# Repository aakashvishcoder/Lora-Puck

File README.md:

# Lora Puck

This is my version of a Lora Puck, which is a compact, low-power wireless communication module that can send and receive data from several kilometers away! This puck has several unique features and parts (as listed below), and includes a temperature sensor as well! This is one of my first ever PCBs, so it most definitely has some flaws!

# Features:
- USBC Receptacle
- Programmable Microcontroller

# Images:

# Build of Materials (BOM)

| Item | Description | Qty | Product link | Price w/ Tax ($) | Running Total |
|------|-------------|-----|--------------|------------------|---------------|
| Capacitor | 100nF (0.1uF) | 13 | [link](https://jlcpcb.com/partdetail/1877-CL05B104KO5NNNC/C1525) | $0.21 | $0.21 |
| Capacitor | 1uF | 2 | [link](https://jlcpcb.com/partdetail/53938-CL05A105KA5NQNC/C52923) | $0.06 | $0.27 |
| Capacitor | 47nF | 1 | [link](https://jlcpcb.com/partdetail/YAGEO-CC0402KRX7R9BB473/C1532) | $0.02 | $0.29 |
| Capacitor | 47pF | 1 | [link](https://jlcpcb.com/partdetail/YAGEO-CC0402JRNPO9BN470/C1549) | $0.01 | $0.30 |
| Capacitor | 1nF | 1 | [link](https://jlcpcb.com/partdetail/YAGEO-CC0402KRX7R9BB102/C1522) | $0.01 | $0.31 |
| Capacitor | 39pF | 1 | [link](https://jlcpcb.com/partdetail/YAGEO-CC0402JRNPO9BN390/C1548) | $0.01 | $0.32 |
| Capacitor | 3.3pF | 4 | [link](https://jlcpcb.com/partdetail/YAGEO-CC0402JRNPO9BN3R3/C1546) | $0.04 | $0.36 |
| Capacitor | 10uF | 2 | [link](https://jlcpcb.com/partdetail/SamsungElectro-CL05A106MQ5NUNC/C15525) | $0.06 | $0.42 |
| Capacitor | 470nF | 1 | [link](https://jlcpcb.com/partdetail/YAGEO-CC0402KRX7R9BB471/C1779) | $0.02 | $0.44 |
| Inductor | 15uH | 1 | [link](https://jlcpcb.com/partdetail/Sunlord-SDCL1005C150KTDF/C285676) | $0.05 | $0.49 |
| Inductor | 47nH | 1 | [link](https://jlcpcb.com/partdetail/JohansonTech-L-0402_47nH/C284438) | $0.05 | $0.54 |
| Inductor | 9.1nH | 1 | [link](https://jlcpcb.com/partdetail/JohansonTech-L-0402_9_1nH/C284437) | $0.05 | $0.59 |
| Ferrite Bead | Ferrite 0402 | 1 | [link](https://jlcpcb.com/partdetail/Sunlord-SDCL1005C4N7STDF/C8589) | $0.01 | $0.60 |
| Balun | Johanson 0900FM15K0039 | 1 | [link](https://jlcpcb.com/partdetail/JohansonTech-0900FM15K0039/C284439) | $0.85 | $1.45 |
| Resistor | 10k | 1 | [link](https://jlcpcb.com/partdetail/UNIROYAL-0402WGF1002TCE/C25804) | $0.01 | $1.46 |
| Resistor | 4.7k | 2 | [link](https://jlcpcb.com/partdetail/UNIROYAL-0402WGF4701TCE/C25867) | $0.02 | $1.48 |
| Resistor | 27.4Ω | 2 | [link](https://jlcpcb.com/partdetail/UNIROYAL-0402WGF270JTCE/C23154) | $0.02 | $1.50 |
| Resistor | 1k | 2 | [link](https://jlcpcb.com/partdetail/UNIROYAL-0402WGF1001TCE/C11702) | $0.02 | $1.52 |
| Resistor | 100Ω | 1 | [link](https://jlcpcb.com/partdetail/UNIROYAL-0402WGF1000TCE/C25086) | $0.01 | $1.53 |
| Resistor | 5.1k | 2 | [link](https://jlcpcb.com/partdetail/UNIROYAL-0402WGF5101TCE/C25905) | $0.02 | $1.55 |
| Switch | Tactile Button | 2 | [link](https://jlcpcb.com/partdetail/XKBConnectivity-TS1187ABAB/C318884) | $0.84 | $2.39 |
| USB Receptacle | USB-C 16P | 1 | [link](https://jlcpcb.com/partdetail/Korean_HropartsElec-TYPEC31M12/C165948) | $0.85 | $3.24 |
| IC | LoRa SX1262 | 1 | [link](https://jlcpcb.com/partdetail/Semtech-SX1262IMLTRT/C967207) | $6.50 | $9.74 |
| IC | RP2040 MCU | 1 | [link](https://jlcpcb.com/partdetail/RaspberryPi-RP2040/C2040) | $4.58 | $14.32 |
| IC | Flash W25Q128JVS | 1 | [link](https://jlcpcb.com/partdetail/Winbond-W25Q128JVSIQ/C97521) | $2.67 | $16.99 |
| IC | RF Switch PE4259 | 1 | [link](https://jlcpcb.com/partdetail/PeregrineSemiconductor-PE4259/C285440) | $1.20 | $18.19 |
| IC | Regulator AP2112K-3.3 | 1 | [link](https://jlcpcb.com/partdetail/DiodesInc-AP2112K3_3TRG1/C15630) | $0.12 | $18.31 |
| Sensor | SHTC3 Humidity/Temp | 1 | [link](https://jlcpcb.com/partdetail/Sensirion-SHTC3/C2844388) | $2.80 | $21.11 |
| Crystal | 32MHz 3225 | 1 | [link](https://jlcpcb.com/partdetail/YXC-X322532MSB4SI/C9003) | $0.32 | $21.43 |
| Crystal | 12MHz 3225 | 1 | [link](https://jlcpcb.com/partdetail/YXC-X322512MSB4SI/C9002) | $0.32 | $21.75 |
| LoRa-Puck PCB | PCBA board assembly | 1 | [link](https://cart.jlcpcb.com/) | $43.94 | $65.69 |

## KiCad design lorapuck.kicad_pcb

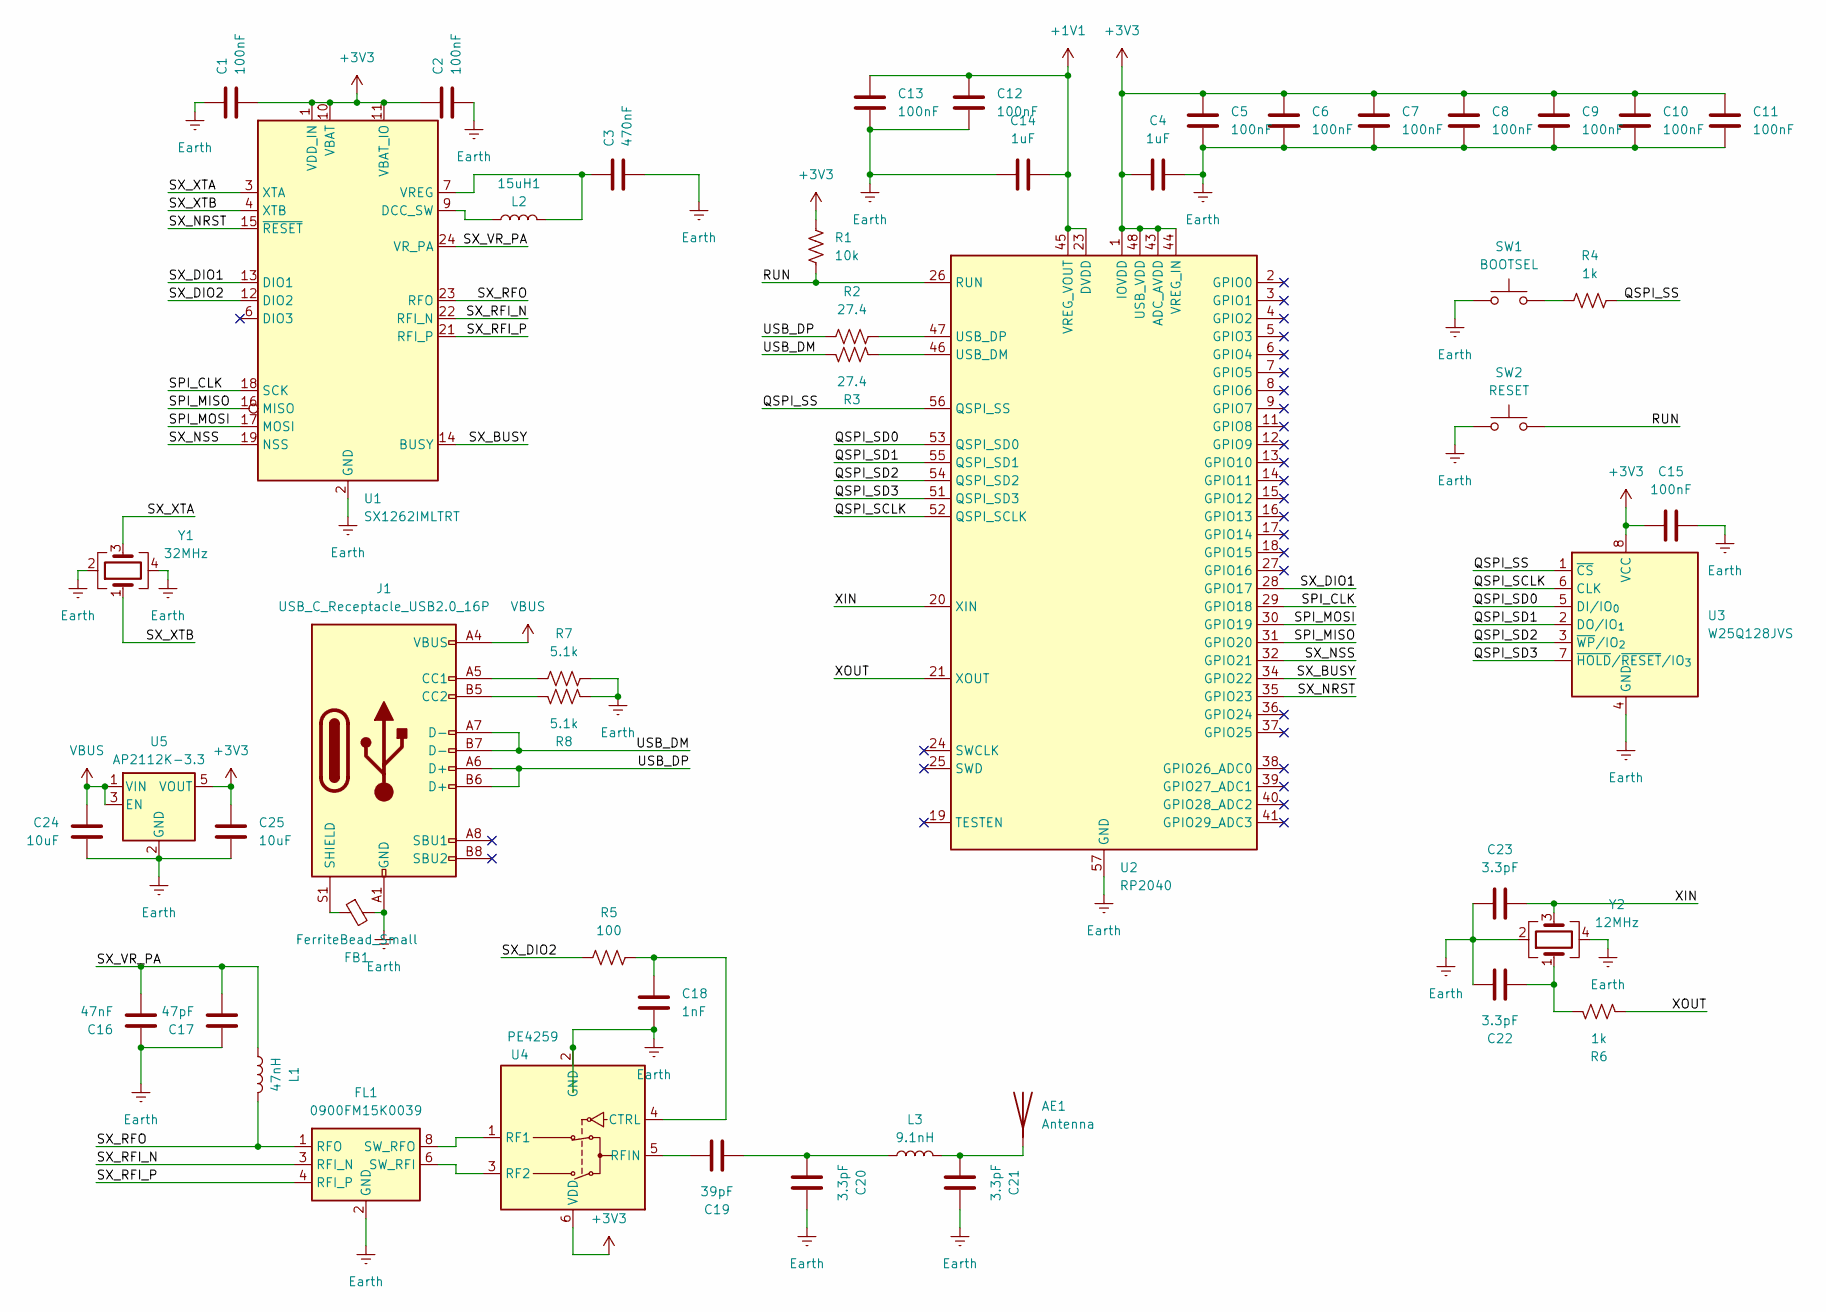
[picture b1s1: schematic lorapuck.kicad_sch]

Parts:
15uH1: L2; L_0402_1005Metric
AE1: Antenna; PinSocket_1x01_P2.54mm_Vertical
C1, C2, C5, C6, C7, C8, C9, C10, C11, C12, C13, C15: 100nF; C_0402_1005Metric
C3: 470nF; C_0402_1005Metric
C4, C14: 1uF; C_0402_1005Metric
C16: 47nF; C_0402_1005Metric
C17: 47pF; C_0402_1005Metric
C18: 1nF; C_0402_1005Metric
C19: 39pF; C_0402_1005Metric
C20, C21, C22, C23: 3.3pF; C_0402_1005Metric
C24, C25: 10uF; C_0402_1005Metric
FB1: FerriteBead_Small; L_0402_1005Metric
FL1: 0900FM15K0039; Balun_Johanson_0900FM15K0039
J1: USB_C_Receptacle_USB2.0_16P; USB_C_Receptacle_GCT_USB4105-xx-A_16P_TopMnt_Horizontal
L1: 47nH; L_0402_1005Metric
L3: 9.1nH; L_0402_1005Metric
R1: 10k; R_0402_1005Metric
R2, R3: 27.4; R_0402_1005Metric
R4, R6: 1k; R_0402_1005Metric
R5: 100; R_0402_1005Metric
R7, R8: 5.1k; R_0402_1005Metric
SW1: BOOTSEL; SW_Tactile_SPST_NO_Straight_CK_PTS636Sx25SMTRLFS
SW2: RESET; SW_Tactile_SPST_NO_Straight_CK_PTS636Sx25SMTRLFS
U1: SX1262IMLTRT; QFN-24-1EP_4x4mm_P0.5mm_EP2.6x2.6mm
U2: RP2040; QFN-56-1EP_7x7mm_P0.4mm_EP3.2x3.2mm
U3: W25Q128JVS; SOIC-8_5.3x5.3mm_P1.27mm
U4: PE4259; SOT-363_SC-70-6
U5: AP2112K-3.3; SOT-23-5
Y1: 32MHz; Crystal_SMD_3225-4Pin_3.2x2.5mm
Y2: 12MHz; Crystal_SMD_Abracon_ABM8G-4Pin_3.2x2.5mm

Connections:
+1V1: C12.2, C13.2, C14.2, U2.23 (DVDD), U2.45 (VREG_VOUT), U2.50 (DVDD)
+3V3: C1.2, C2.1, C4.1, C5.2, C6.2, C7.2, C8.2, C9.2, C10.2, C11.2, C15.2, C25.1, R1.1, U1.1 (VDD_IN), U1.10 (VBAT), U1.11 (VBAT_IO), U2.1 (IOVDD), U2.10 (IOVDD), U2.22 (IOVDD), U2.33 (IOVDD), U2.42 (IOVDD), U2.43 (ADC_AVDD), U2.44 (VREG_IN), U2.48 (USB_VDD), U2.49 (IOVDD), U3.8 (VCC), U4.6 (VDD), U5.5 (VOUT); also elsewhere on the board
/<NO NET>: U1.15 (~RESET), U2.35 (GPIO23)
/IO0: U2.2 (GPIO0); also elsewhere on the board
/IO1: U2.3 (GPIO1); also elsewhere on the board
/QSPI_SCLK: U2.52 (QSPI_SCLK), U3.6 (CLK)
/QSPI_SD0: U2.53 (QSPI_SD0), U3.5 (DI/IO_{0})
/QSPI_SD1: U2.55 (QSPI_SD1), U3.2 (DO/IO_{1})
/QSPI_SD2: U2.54 (QSPI_SD2), U3.3 (~WP/IO_{2})
/QSPI_SD3: U2.51 (QSPI_SD3), U3.7 (~HOLD/~RESET/IO_{3})
/QSPI_SS: R4.1, U2.56 (QSPI_SS), U3.1 (~CS)
/RUN: R1.2, SW2.2, U2.26 (RUN)
/SPI_CLK: U1.18 (SCK), U2.29 (GPIO18)
/SPI_MISO: U1.16 (MISO), U2.31 (GPIO20)
/SPI_MOSI: U1.17 (MOSI), U2.30 (GPIO19)
/SX_BUSY: U1.14 (BUSY), U2.34 (GPIO22)
/SX_DIO1: U1.13 (DIO1), U2.28 (GPIO17)
/SX_DIO2: R5.1, U1.12 (DIO2)
/SX_NSS: U1.19 (NSS), U2.32 (GPIO21)
/SX_RFI_N: FL1.3 (RFI_N), U1.22 (RFI_N)
/SX_RFI_P: FL1.4 (RFI_P), U1.21 (RFI_P)
/SX_RFO: FL1.1 (RFO), L1.2, U1.23 (RFO)
/SX_VR_PA: C16.2, C17.2, L1.1, U1.24 (VR_PA)
/SX_XTA: U1.3 (XTA), Y1.3
/SX_XTB: U1.4 (XTB), Y1.1
/USB_DM: J1.A7 (D-), J1.B7 (D-), R3.2
/USB_DP: J1.A6 (D+), J1.B6 (D+), R2.2
/XIN: C23.1, U2.20 (XIN), Y2.3
/XOUT: R6.2, U2.21 (XOUT)
Earth: C1.1, C2.2, C3.2, C4.2, C5.1, C6.1, C7.1, C8.1, C9.1, C10.1, C11.1, C12.1, C13.1, C14.1, C15.1, C16.1, C17.1, C18.2, C20.1, C21.1, C22.1, C23.2, C24.2, C25.2, FB1.2, FL1.2 (GND), FL1.5 (GND), FL1.7 (GND), FL1.9 (GND), FL1.10 (GND), J1.A1 (GND), J1.A12 (GND), J1.B1 (GND), J1.B12 (GND), R7.2, R8.2, SW1.1, SW2.1, U1.2 (GND), U1.5 (GND), U1.8 (GND), U1.20 (GND), U1.25 (GND), U2.57 (GND), U3.4 (GND), U4.2 (GND), U5.2 (GND), Y1.2, Y1.4, Y2.2, Y2.4; also elsewhere on the board
unnamed: AE1.1 (A), C21.2, L3.2
unnamed: C19.2, C20.2, L3.1
unnamed: C22.2, R6.1, Y2.1
unnamed: FL1.6 (SW_RFI), U4.3 (RF2)
unnamed: FL1.8 (SW_RFO), U4.1 (RF1)
unnamed: J1.A5 (CC1), R7.1
unnamed: J1.B5 (CC2), R8.1
unnamed: FB1.1, J1.S1 (SHIELD)
unnamed: R4.2, SW1.2
unnamed: 15uH1.1, U1.9 (DCC_SW)
unnamed: 15uH1.2, C3.1, U1.7 (VREG)
unnamed: R3.1, U2.46 (USB_DM)
unnamed: R2.1, U2.47 (USB_DP)
unnamed: C18.1, R5.2, U4.4 (CTRL)
unnamed: C19.1, U4.5 (RFIN)
VBUS: C24.1, J1.A4 (VBUS), J1.A9 (VBUS), J1.B4 (VBUS), J1.B9 (VBUS), U5.1 (VIN), U5.3 (EN)

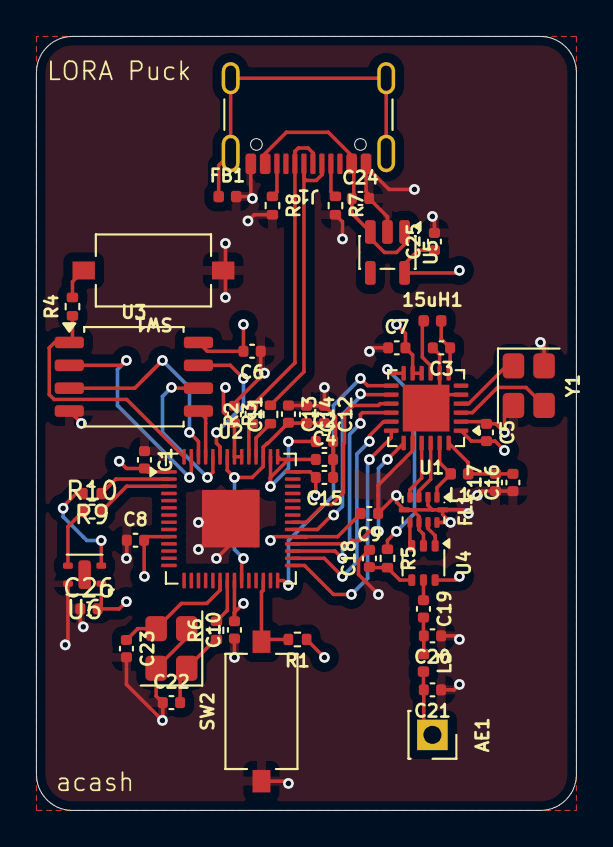
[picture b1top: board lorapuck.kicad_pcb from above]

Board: 4 copper layers, 30.0 x 43.0 mm, 53 parts (0 on the bottom side), 48 nets.

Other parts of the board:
C26: 100nF; C_0402_1005Metric
R9, R10: 4.7k; R_0402_1005Metric
U6: SHTC3; Sensirion_DFN-4-1EP_2x2mm_P1mm_EP0.7x1.6mm

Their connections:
+3V3: C26.2, U6.1 (VDD); also elsewhere on the board
/IO0: R9.1; also elsewhere on the board
/IO1: R10.2; also elsewhere on the board
Earth: C26.1, U6.4 (VSS); also elsewhere on the board
unnamed: R9.2, U6.2 (SCL)
unnamed: R10.1, U6.3 (SDA)

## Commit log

2025-11-28 all the kicad files added
2025-11-30 Add initial README for Lora PUCK project
2025-11-30 Enhance README with features and images
    Added features and images sections to README.
2025-11-30 Fix spelling of 'Puck' in README
2025-12-01 edited the usbc receptacle and added a weather sensor!
2025-12-01 quick change to the pcb
2025-12-01 Update BOM with SHTC3 datasheet link
    Added datasheet link for SHTC3 sensor in the BOM.
2025-12-03 added gerber + fixed gitignore + finished bom
2025-12-03 Revise BOM section in README.md
    Updated the Bill of Materials (BOM) section with new item details, including descriptions, quantities, product links, and prices.
2025-12-03 changed the file name
2025-12-03 cleaned up the files
2025-12-04 fixed some issues with pcb
